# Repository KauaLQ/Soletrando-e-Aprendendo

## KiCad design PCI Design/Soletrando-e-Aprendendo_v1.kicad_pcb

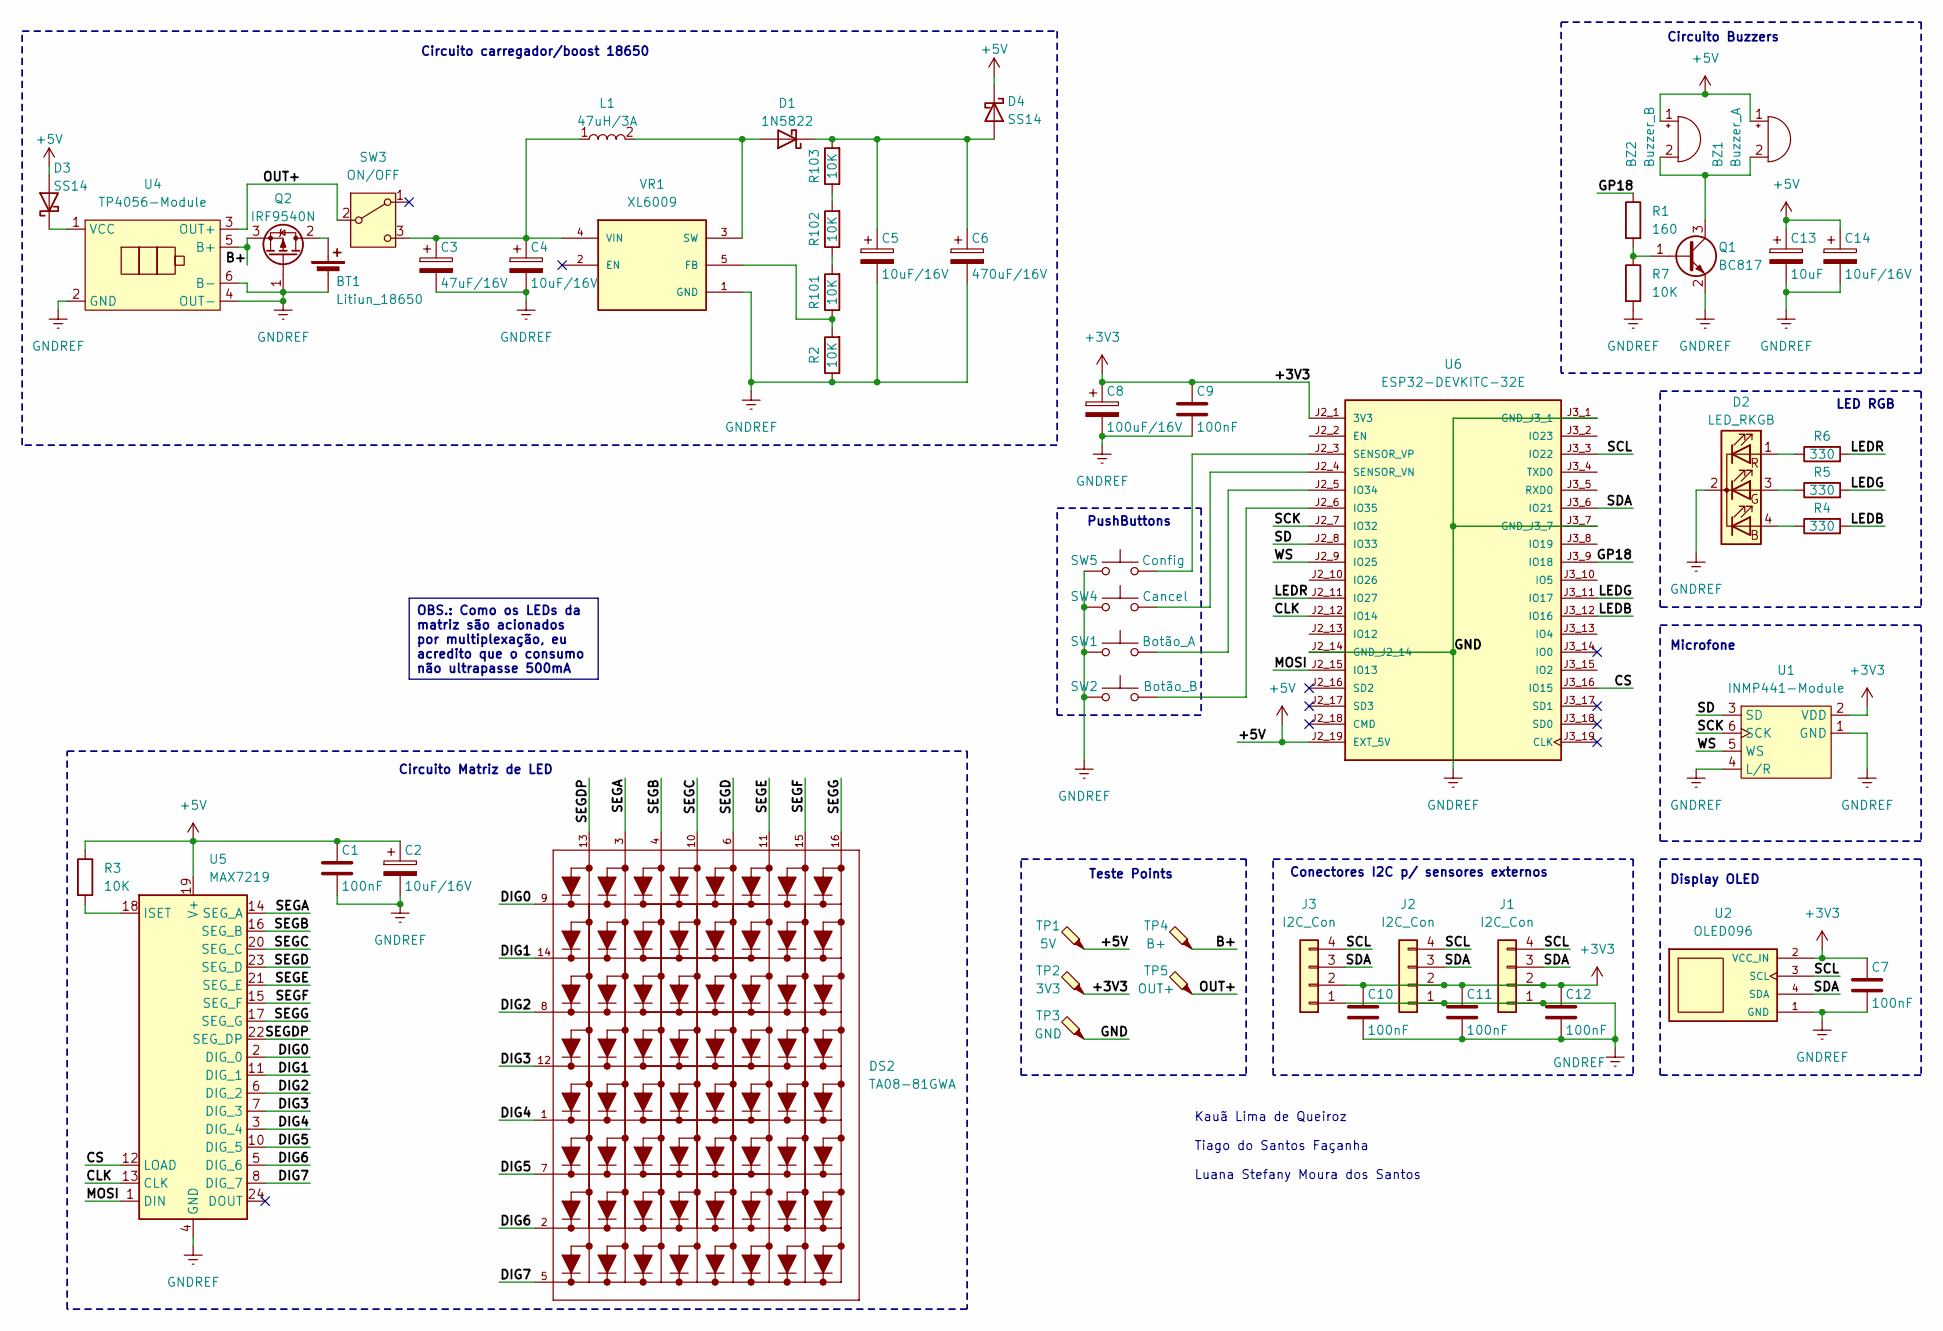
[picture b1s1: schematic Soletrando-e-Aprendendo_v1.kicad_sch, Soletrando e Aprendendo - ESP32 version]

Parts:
BT1: Litiun_18650; BatteryHolder_Keystone_1042_1x18650
BZ1: Buzzer_A; Buzzer_12x9.5RM7.6
BZ2: Buzzer_B; Buzzer_12x9.5RM7.6
C1, C7, C9, C10, C11, C12: 100nF; C_0805_2012Metric
C2, C4, C5, C14: 10uF/16V; CP_Elec_5x5.4
C3: 47uF/16V; CP_Radial_D5.0mm_P2.50mm
C6: 470uF/16V; CP_Radial_D8.0mm_P3.80mm
C8: 100uF/16V; CP_Radial_D5.0mm_P2.50mm
C13: 10uF; CP_Elec_5x5.4
D1: 1N5822; D_DO-201AD_P15.24mm_Horizontal
D2: LED_RKGB; LED_D5.0mm-4_RGB
D3, D4: SS14; D_SMA
DS2: TA08-81GWA; LED_MATRIX_8X8-32X32MM; PARTREV V.11A
J1, J2, J3: I2C_Con; JST_B4B-XH-A
L1: 47uH/3A; L_Toroid_Vertical_L13.0mm_W6.5mm_P5.60mm; Manufacturer_Part_Number CDRH74NP-220MC-B; Mouser Part Number 851-CDRH74NP-220MC
Q1: BC817; SOT-23
Q2: IRF9540N; TO-220-3_Horizontal_TabDown
R1: 160; R_0805_2012Metric
R2, R101, R102, R103: 10K; R_Axial_DIN0207_L6.3mm_D2.5mm_P10.16mm_Horizontal
R3, R7: 10K; R_0805_2012Metric
R4, R5, R6: 330; R_0805_2012Metric
SW1: Botão_A; SW_PUSH_6mm_H7.3mm
SW2: Botão_B; SW_PUSH_6mm_H7.3mm
SW3: ON/OFF; SW_Slide_SPDT_Straight_CK_OS102011MS2Q
SW4: Cancel; SW_PUSH_6mm_H7.3mm
SW5: Config; SW_PUSH_6mm_H7.3mm
TP1: 5V; TestPoint_THTPad_D2.0mm_Drill1.0mm
TP2: 3V3; TestPoint_THTPad_D2.0mm_Drill1.0mm
TP3: GND; TestPoint_THTPad_D2.0mm_Drill1.0mm
TP4: B+; TestPoint_THTPad_D2.0mm_Drill1.0mm
TP5: OUT+; TestPoint_THTPad_D2.0mm_Drill1.0mm
U1: INMP441-Module
U2: OLED096; MODULE_DM-OLED096-636; PARTREV 2018-09-10
U4: TP4056-Module
U5: MAX7219; DIP-24_W7.62mm
U6: ESP32-DEVKITC-32E; DOUBLE_MODULE_DEVKIT; PARTREV 1.4
VR1: XL6009; DPAK170P1435X465-6N; PARTREV 1.1

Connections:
+3V3: C7.1, C8.1, C9.1, C10.1, C11.1, C12.1, J1.2, J2.2, J3.2, TP2.1, U1.2 (VDD), U2.2 (VCC_IN), U6.J2_1 (3V3)
+5V: BZ1.1 (+), BZ2.1 (+), C1.1, C2.1, C13.1, C14.1, D3.2 (A), D4.1 (K), R3.1, TP1.1, U5.19 (V+), U6.J2_19 (EXT_5V)
/B+: Q2.3 (S), TP4.1, U4.5 (B+)
/CLK: U5.13 (CLK), U6.J2_12 (IO14)
/CS: U5.12 (LOAD), U6.J3_16 (IO15)
/DIG0: DS2.9, U5.2 (DIG_0)
/DIG1: DS2.14, U5.11 (DIG_1)
/DIG2: DS2.8, U5.6 (DIG_2)
/DIG3: DS2.12, U5.7 (DIG_3)
/DIG4: DS2.1, U5.3 (DIG_4)
/DIG5: DS2.7, U5.10 (DIG_5)
/DIG6: DS2.2, U5.5 (DIG_6)
/DIG7: DS2.5, U5.8 (DIG_7)
/GP18: R1.1, U6.J3_9 (IO18)
/LEDB: R4.2, U6.J3_12 (IO16)
/LEDG: R5.2, U6.J3_11 (IO17)
/LEDR: R6.2, U6.J2_11 (IO27)
/MOSI: U5.1 (DIN), U6.J2_15 (IO13)
/OUT+: SW3.2 (B), TP5.1, U4.3 (OUT+)
/SCK: U1.6 (SCK), U6.J2_7 (IO32)
/SCL: J1.4, J2.4, J3.4, U2.3 (SCL), U6.J3_3 (IO22)
/SD: U1.3 (SD), U6.J2_8 (IO33)
/SDA: J1.3, J2.3, J3.3, U2.4 (SDA), U6.J3_6 (IO21)
/SEGA: DS2.3, U5.14 (SEG_A)
/SEGB: DS2.4, U5.16 (SEG_B)
/SEGC: DS2.10, U5.20 (SEG_C)
/SEGD: DS2.6, U5.23 (SEG_D)
/SEGDP: DS2.13, U5.22 (SEG_DP)
/SEGE: DS2.11, U5.21 (SEG_E)
/SEGF: DS2.15, U5.15 (SEG_F)
/SEGG: DS2.16, U5.17 (SEG_G)
/WS: U1.5 (WS), U6.J2_9 (IO25)
GNDREF: BT1.2 (-), C1.2, C2.2, C3.2, C4.2, C5.2, C6.2, C7.2, C8.2, C9.2, C10.2, C11.2, C12.2, C13.2, C14.2, D2.2 (K), J1.1, J2.1, J3.1, Q1.2 (E), Q2.1 (G), R2.1, R7.2, SW1.1, SW2.1, SW4.1, SW5.1, TP3.1, U1.1 (GND), U1.4 (L/R), U2.1 (GND), U4.2 (GND), U4.4 (OUT-), U4.6 (B-), U5.4 (GND), U5.9 (GND), U6.J2_14 (GND_J2_14), U6.J3_1 (GND_J3_1), U6.J3_7 (GND_J3_7), VR1.1 (GND)
unnamed: BT1.1 (+), Q2.2 (D)
unnamed: BZ1.2 (-), BZ2.2 (-), Q1.3 (C)
unnamed: D1.2 (A), L1.2, VR1.3 (SW), VR1.6 (SW)
unnamed: C5.1, C6.1, D1.1 (K), D4.2 (A), R103.2
unnamed: D2.4 (BA), R4.1
unnamed: D2.3 (GA), R5.1
unnamed: D2.1 (RA), R6.1
unnamed: D3.1 (K), U4.1 (VCC)
unnamed: Q1.1 (B), R1.2, R7.1
unnamed: R101.2, R102.1
unnamed: R102.2, R103.1
unnamed: C3.1, C4.1, L1.1, SW3.3 (C), VR1.4 (VIN)
unnamed: R3.2, U5.18 (ISET)
unnamed: SW1.2, U6.J2_5 (IO34)
unnamed: SW2.2, U6.J2_6 (IO35)
unnamed: SW4.2, U6.J2_4 (SENSOR_VN)
unnamed: SW5.2, U6.J2_3 (SENSOR_VP)
unnamed: R2.2, R101.1, VR1.5 (FB)

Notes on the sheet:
Circuito carregador/boost 18650
Circuito Matriz de LED
Conectores I2C p/ sensores externos
Display OLED
Circuito Buzzers
LED RGB
Kauã Lima de Queiroz Tiago do Santos Façanha Luana Stefany Moura dos Santos
PushButtons
Teste Points
Microfone
OBS.: Como os LEDs da matriz são acionados por multiplexação, eu acredito que o consumo não ultrapasse 500mA

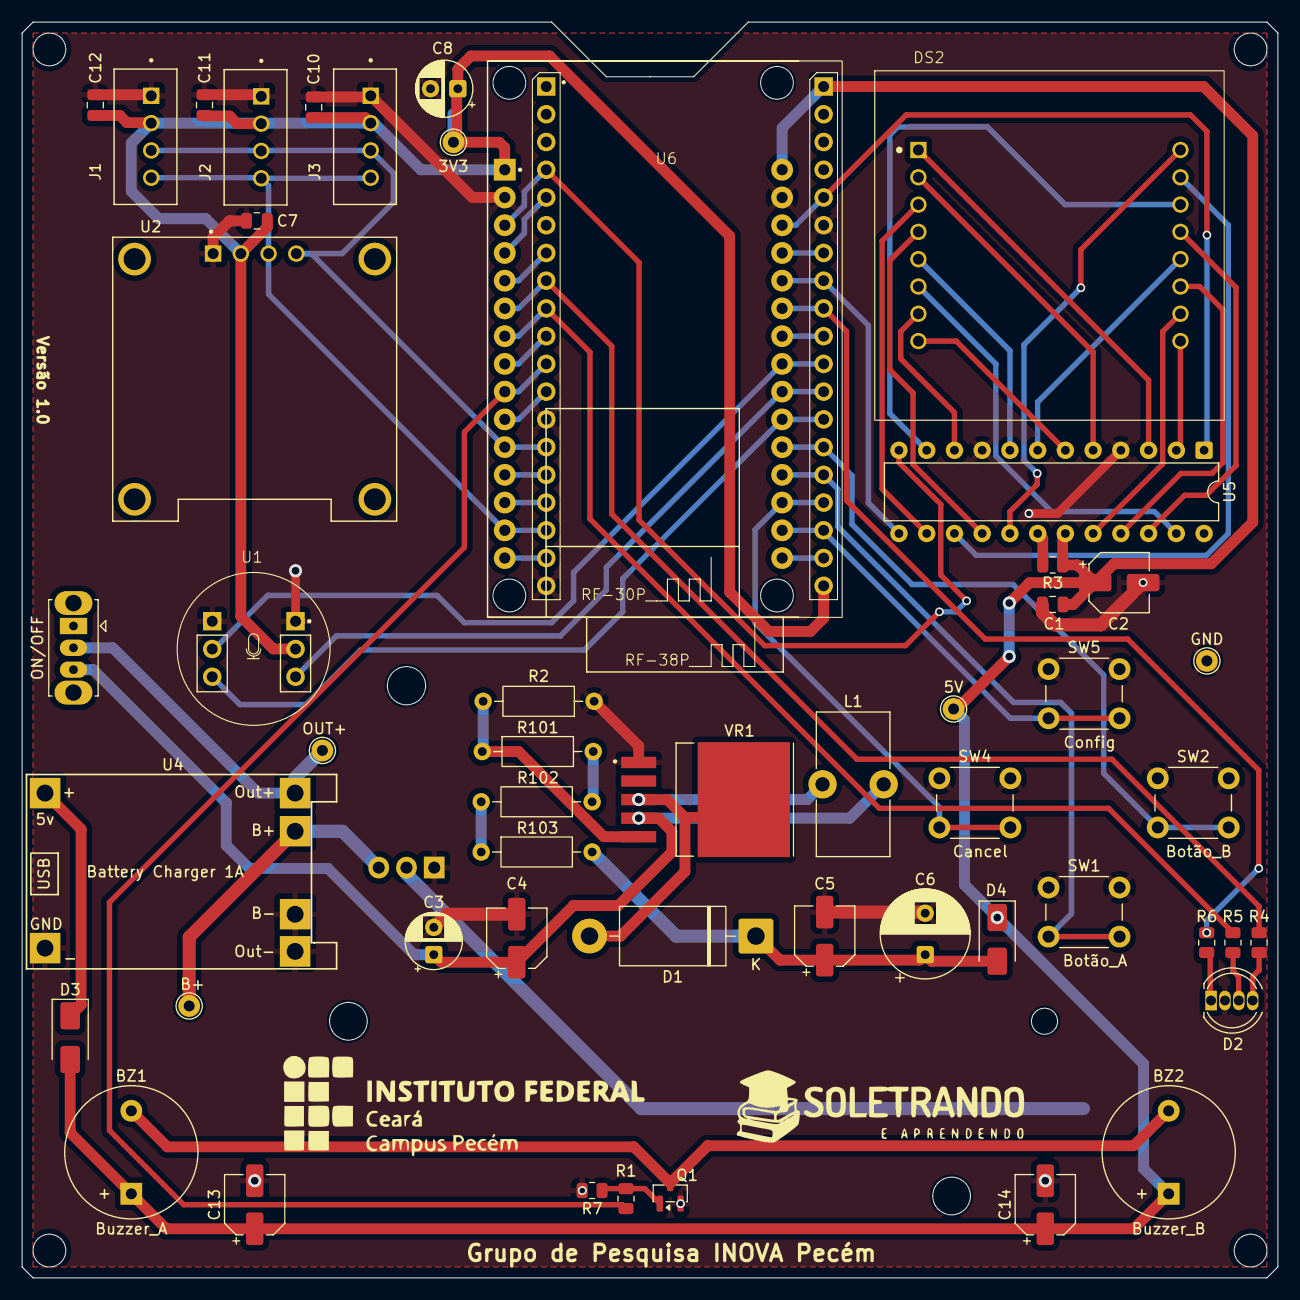
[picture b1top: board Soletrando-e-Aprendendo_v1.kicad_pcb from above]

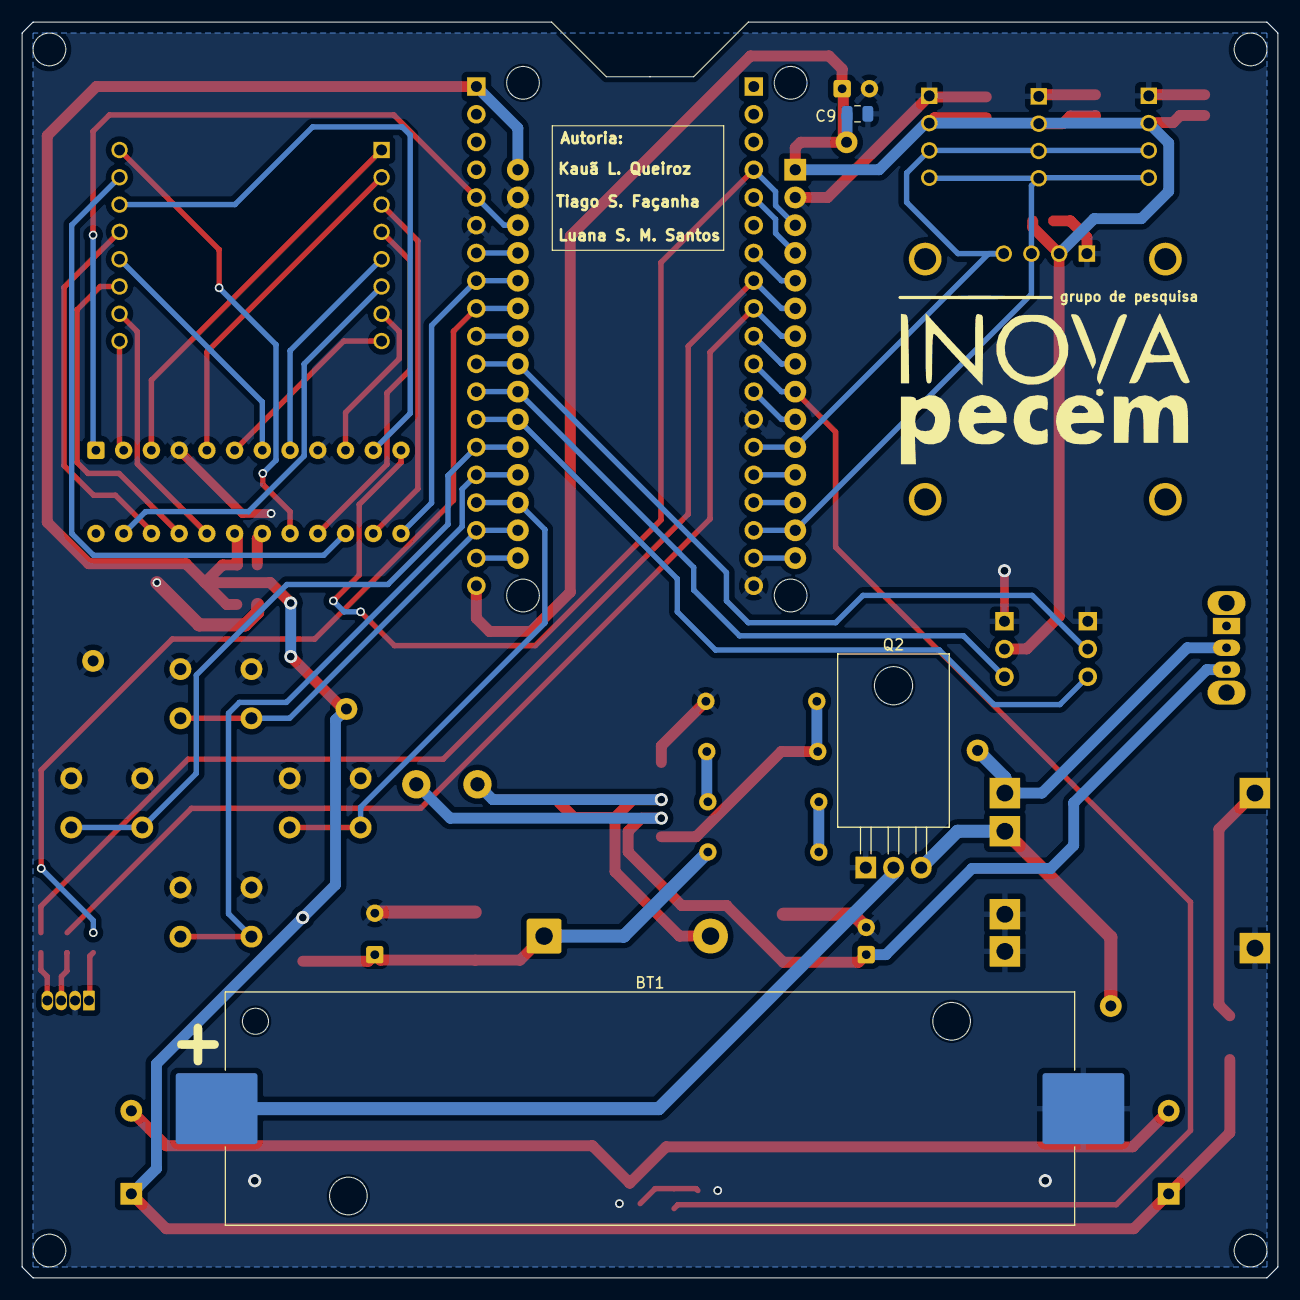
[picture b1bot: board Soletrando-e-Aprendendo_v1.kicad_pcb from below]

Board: 2 copper layers, 115.0 x 115.0 mm, 54 parts (3 on the bottom side), 51 nets.

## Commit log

2026-05-07 Primeiro commit: Projeto da PCI
2026-05-12 Adicionando novos capacitores no circuito
2026-05-13 Adicionando novas serigrafias
2026-05-13 Gerando arquivos Gerbers
2026-05-13 Adicionando plano GND ao TopOverLayer
